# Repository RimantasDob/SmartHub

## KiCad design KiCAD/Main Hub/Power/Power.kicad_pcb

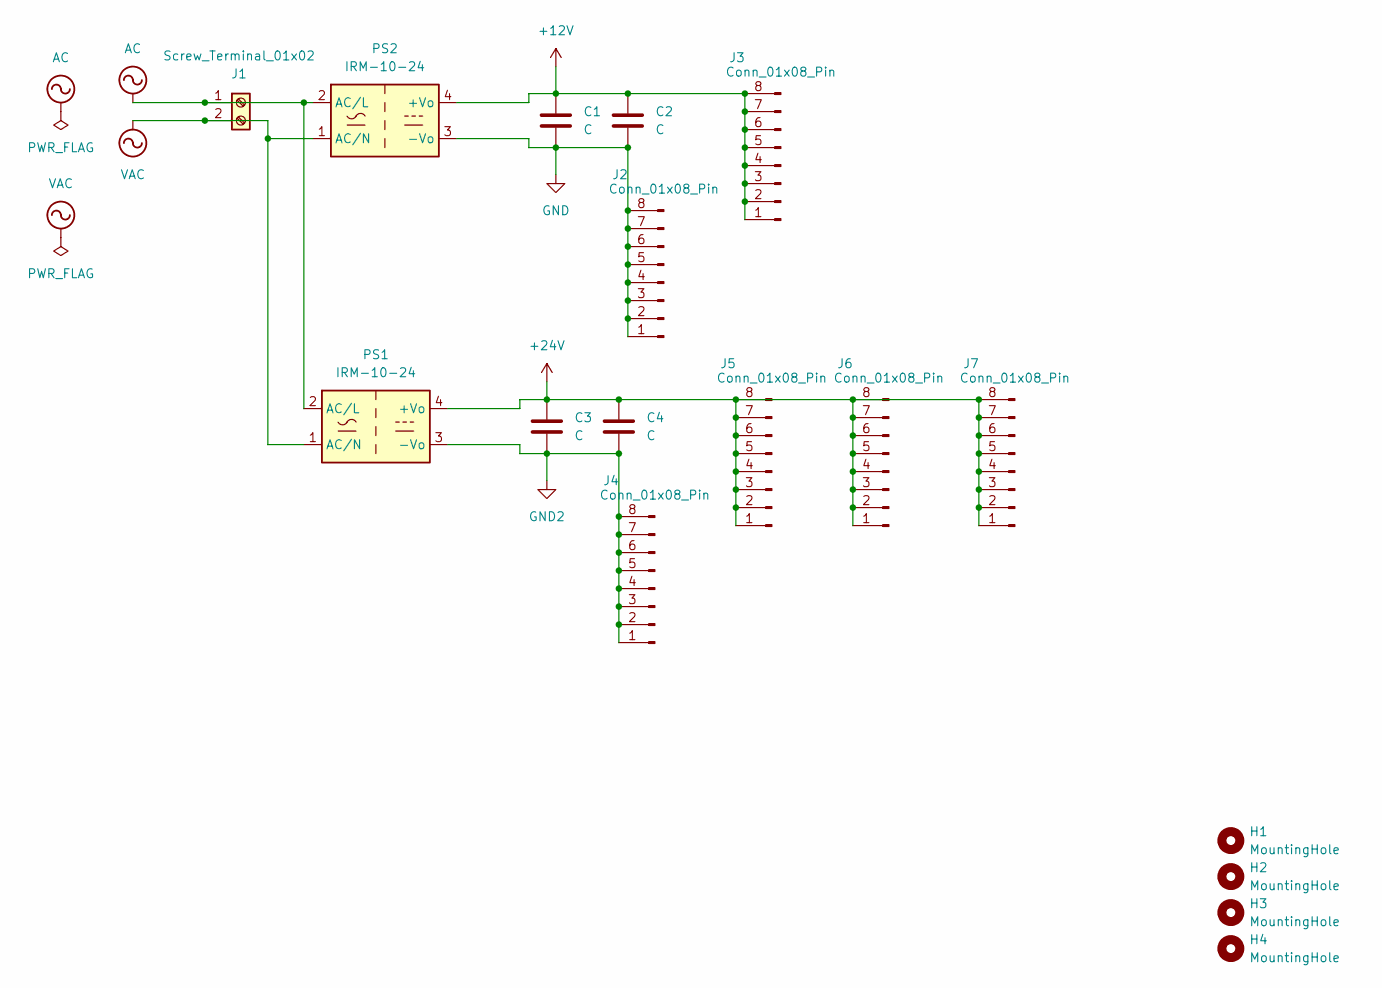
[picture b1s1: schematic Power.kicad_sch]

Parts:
C1, C3: C; CP_Radial_D6.3mm_P2.50mm
C2, C4: C; C_0805_2012Metric_Pad1.18x1.45mm_HandSolder
H1, H2, H3, H4: MountingHole; MountingHole_3.2mm_M3_DIN965
J1: Screw_Terminal_01x02; TerminalBlock_Phoenix_MKDS-1,5-2-5.08_1x02_P5.08mm_Horizont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
J2, J3, J4, J5, J6, J7: Conn_01x08_Pin; JST_EH_B8B-EH-A_1x08_P2.50mm_Vertical
PS1, PS2: IRM-10-24; Converter_ACDC_MeanWell_IRM-10-xx_THT

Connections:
+12V: C1.1, C2.1, J3.1, J3.2, J3.3, J3.4, J3.5, J3.6, J3.7, J3.8, PS2.4 (+Vo)
+24V: C3.1, C4.1, J5.1, J5.2, J5.3, J5.4, J5.5, J5.6, J5.7, J5.8, J6.1, J6.2, J6.3, J6.4, J6.5, J6.6, J6.7, J6.8, J7.1, J7.2, J7.3, J7.4, J7.5, J7.6, J7.7, J7.8, PS1.4 (+Vo)
AC: J1.1, PS1.2 (AC/L), PS2.2 (AC/L)
GND: C1.2, C2.2, J2.1, J2.2, J2.3, J2.4, J2.5, J2.6, J2.7, J2.8, PS2.3 (-Vo)
GND2: C3.2, C4.2, J4.1, J4.2, J4.3, J4.4, J4.5, J4.6, J4.7, J4.8, PS1.3 (-Vo)
VAC: J1.2, PS1.1 (AC/N), PS2.1 (AC/N)

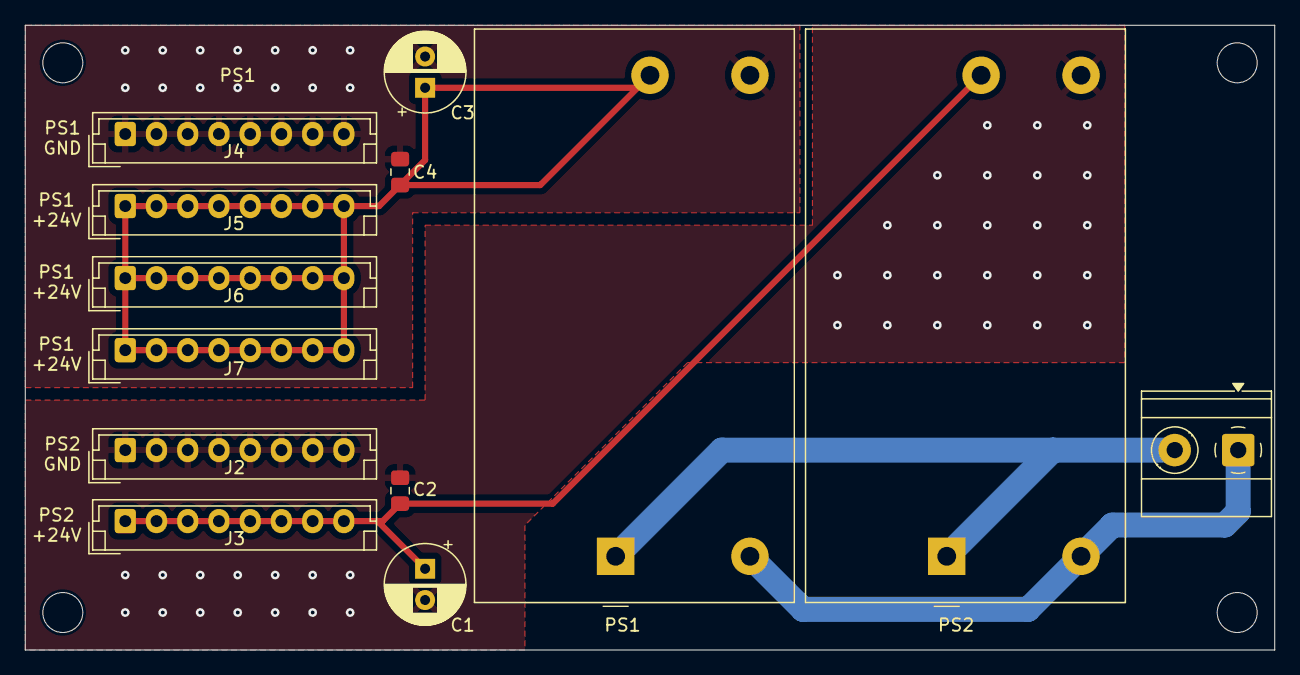
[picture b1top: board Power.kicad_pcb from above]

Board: 2 copper layers, 100.0 x 50.0 mm, 17 parts (0 on the bottom side), 6 nets.

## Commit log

2025-03-20 inital commit v1.1
2025-03-29 PSU pcb
2025-04-05 Horizontal power board
